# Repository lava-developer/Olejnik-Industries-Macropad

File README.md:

# Custom-Macropad

A macropad made by me for personal use

| Case                      | Case - Assembled                              |
| ------------------------- | --------------------------------------------- |
|  |  |

| Schematic                           | PCB                     | PCB - 3D Render               |
| ----------------------------------- | ----------------------- | ----------------------------- |
|  |  |  |

### Why?

My keyboard doesn't have a numpad and I needed more keys for 3D modelling, programming and designing.

### Features

The macropad features 9 programmable keys and a programmable 128x32 OLED display. It runs on the Seeed Studio XIAO RP2040 microcontroller.

### Firmware

The current firmware in the main.py file makes the thing a simple 1-9 numpad but it is easily changeable to serve desired purposes.

### Challenges

For this project I needed to learn KiCad and PCB design, as well as get better at python.

### Specifications

BOM:

- 1x Seeed Studio XIAO RP2040

- 9x Cherry MX Switches

- 9x Blank DSA Keycaps

- 1x SSD1306 0.91" OLED Display

- 4x M3 Heatset Insert

- 4x M3x16 Bolt

Other:

- Custom PCB

- 3D-printed case: [Bottom Case](/CAD/macropad_casebottom), [Top Case](/CAD/macropad_casetop)

- KMK software

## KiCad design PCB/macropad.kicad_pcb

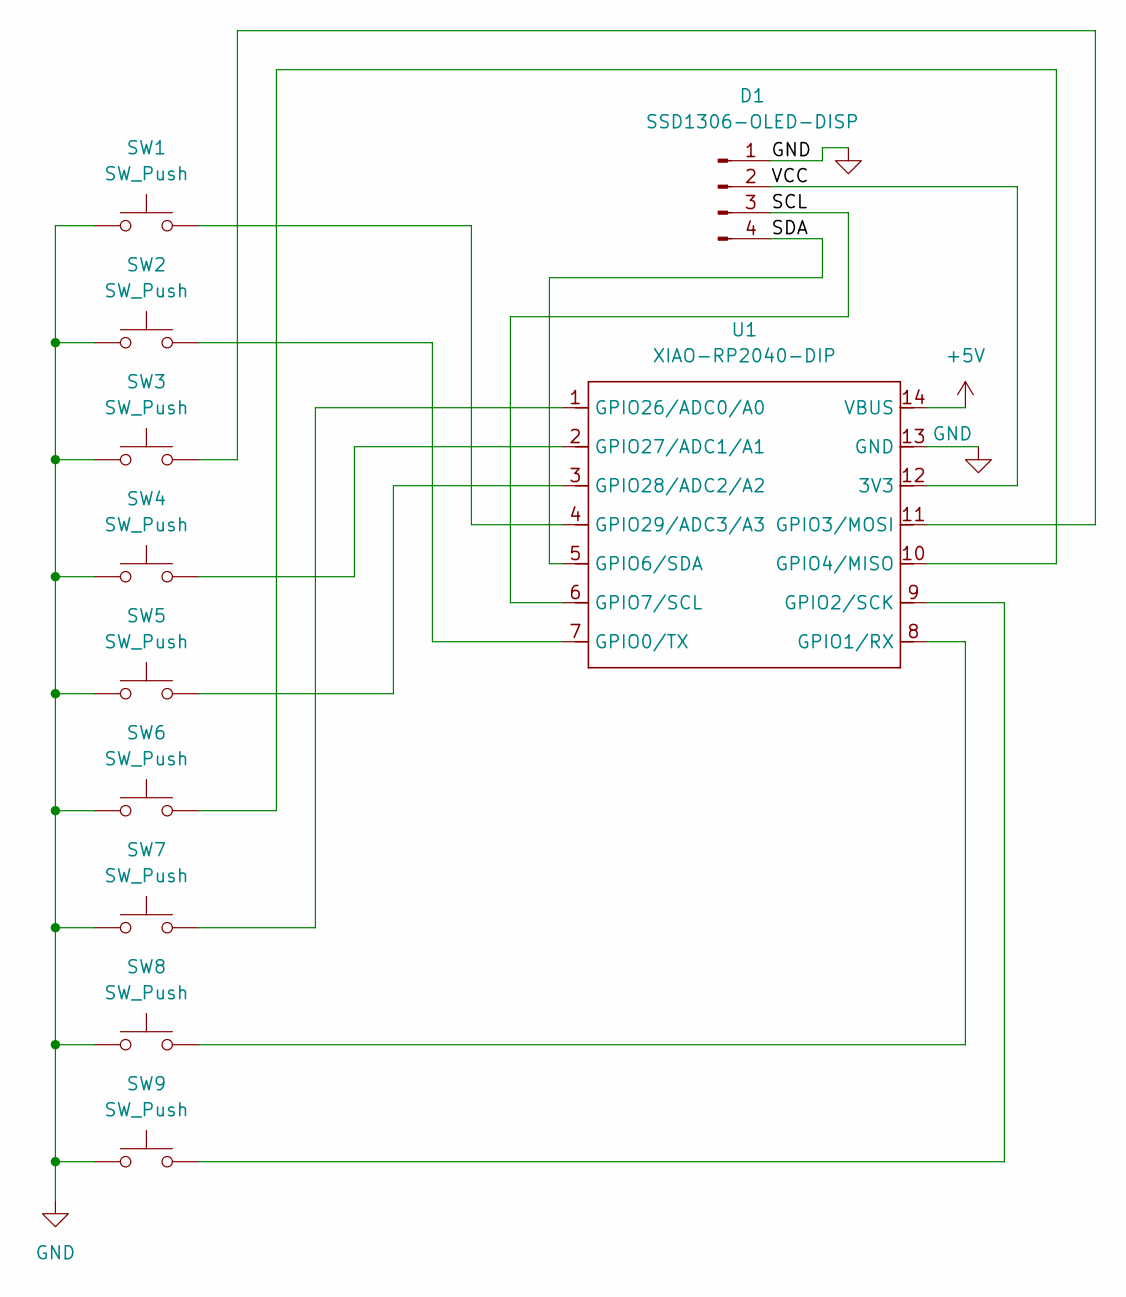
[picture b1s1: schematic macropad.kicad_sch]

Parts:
D1: SSD1306-OLED-DISP; SSD1306-0.91-OLED-4pin-128x32
SW1, SW2, SW3, SW4, SW5, SW6, SW7, SW8, SW9: SW_Push; SW_Cherry_MX_1.00u_PCB
U1: XIAO-RP2040-DIP

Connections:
+5V: U1.14 (VBUS)
/SCL: D1.3, U1.6 (GPIO7/SCL)
/SDA: D1.4, U1.5 (GPIO6/SDA)
/VCC: D1.2, U1.12 (3V3)
GND: D1.1, SW1.1, SW2.1, SW3.1, SW4.1, SW5.1, SW6.1, SW7.1, SW8.1, SW9.1, U1.13 (GND)
unnamed: SW2.2, U1.7 (GPIO0/TX)
unnamed: SW8.2, U1.8 (GPIO1/RX)
unnamed: SW9.2, U1.9 (GPIO2/SCK)
unnamed: SW3.2, U1.11 (GPIO3/MOSI)
unnamed: SW6.2, U1.10 (GPIO4/MISO)
unnamed: SW7.2, U1.1 (GPIO26/ADC0/A0)
unnamed: SW4.2, U1.2 (GPIO27/ADC1/A1)
unnamed: SW5.2, U1.3 (GPIO28/ADC2/A2)
unnamed: SW1.2, U1.4 (GPIO29/ADC3/A3)

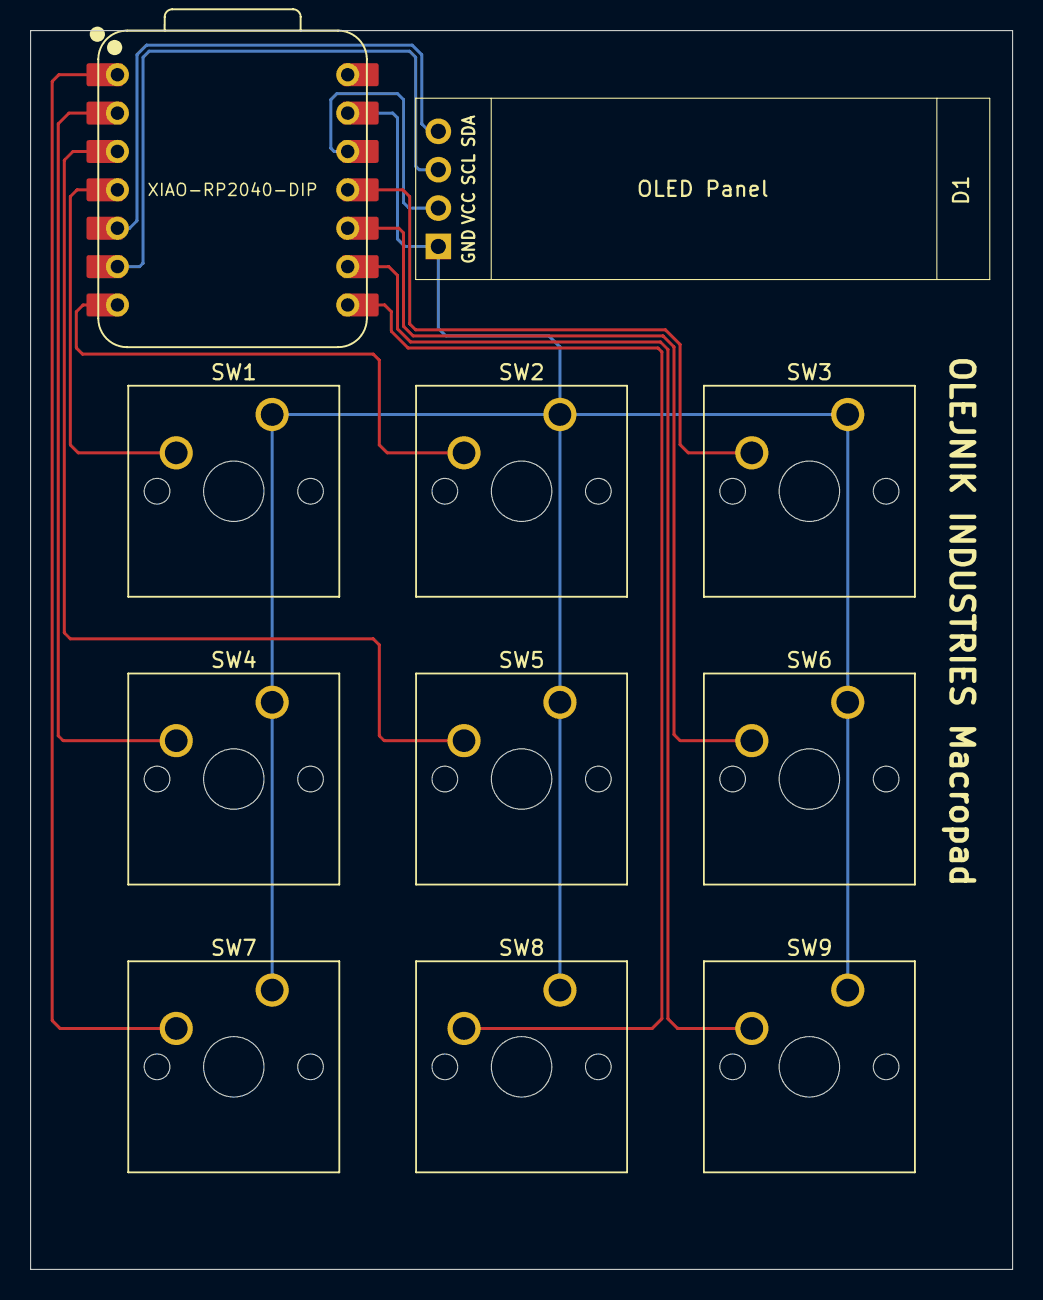
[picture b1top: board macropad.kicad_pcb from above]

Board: 2 copper layers, 65.0 x 82.0 mm, 11 parts (0 on the bottom side), 13 nets.

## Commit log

2025-12-19 First version of PCB
2025-12-19 PCB v.2
2025-12-19 Remove ignored files from repo
2025-12-20 Add GNU General Public License v3
    Added the GNU General Public License version 3 to the project.
2025-12-21 Revert "Add GNU General Public License v3"
    This reverts commit 43e1deb9184c2d37fc6982dc0607ee074dc633d8.
2025-12-21 Add LICENSE file
2025-12-21 Final PCB version
2025-12-21 Added CAD
2025-12-21 Update README
    Added features section to highlight the macropad's capabilities.
2025-12-21 Add firmware
2025-12-23 Add PCB gerbers
2026-01-19 Update case
2026-02-02 Add final photo
2026-02-19 Update extras
